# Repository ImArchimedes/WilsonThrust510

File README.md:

# WilsonThrust510
DIY PC Flight Simulator Throttle.

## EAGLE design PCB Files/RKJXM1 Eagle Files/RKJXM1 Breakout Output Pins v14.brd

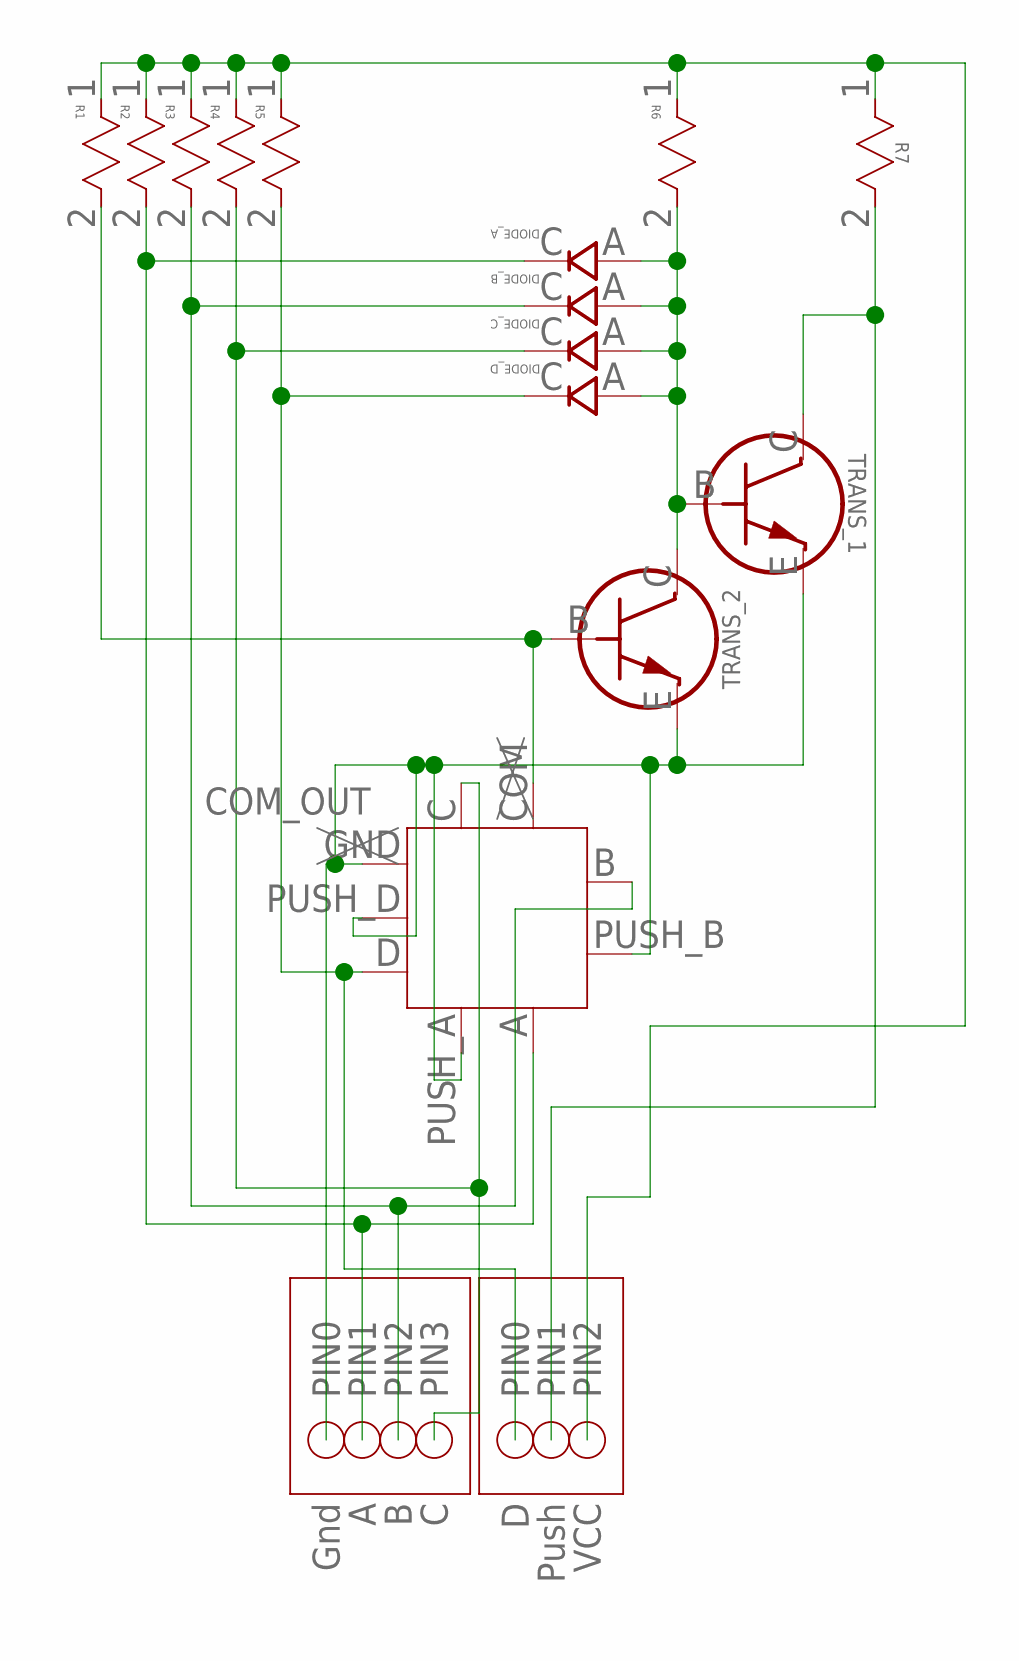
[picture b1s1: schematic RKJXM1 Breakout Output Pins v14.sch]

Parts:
DIODE_A: DIODE_SCHOTTKY_SMD_USC_TOS
DIODE_B: DIODE_SCHOTTKY_SMD_USC_TOS
DIODE_C: DIODE_SCHOTTKY_SMD_USC_TOS
DIODE_D: DIODE_SCHOTTKY_SMD_USC_TOS
R1, R2, R3, R4, R5, R6, R7: RESISTOR_1K_SMD_RNCP0805FTD1K00STA_RNCP0805_STP-L; STA_RNCP0805_STP-L
RKJXM1_SWITCH: RKJXM1_V3; RKJXM1_FOOT_V3; PART_NAME RKJXM1_Switch
TRANS_1, TRANS_2: TRANS_NPN_SMD_MMBT3904-TPSOT-23_MCC-L; SOT-23_MCC-L
U$3: JST_ZH_4PIN
U$4: JST_ZH_3PIN_NO_GND

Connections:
A_OUT: DIODE_A.C, R2.2, RKJXM1_SWITCH.A, U$3.PIN1
B_OUT: DIODE_B.C, R3.2, RKJXM1_SWITCH.B, U$3.PIN2
C_OUT: DIODE_C.C, R4.2, RKJXM1_SWITCH.C, U$3.PIN3
D_OUT: DIODE_D.C, R5.2, RKJXM1_SWITCH.D, U$4.PIN0
GROUND_OUT: RKJXM1_SWITCH.GND, RKJXM1_SWITCH.PUSH_A, RKJXM1_SWITCH.PUSH_B, RKJXM1_SWITCH.PUSH_D, TRANS_1.E, TRANS_2.E, U$3.PIN0
unnamed: R1.2, RKJXM1_SWITCH.COM, TRANS_2.B
unnamed: DIODE_A.A, DIODE_B.A, DIODE_C.A, DIODE_D.A, R6.2, TRANS_1.B, TRANS_2.C
PUSH_OUT: R7.2, TRANS_1.C, U$4.PIN1
VCC_OUT: R1.1, R2.1, R3.1, R4.1, R5.1, R6.1, R7.1, U$4.PIN2

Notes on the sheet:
COM_OUT
VCC
Push
Gnd

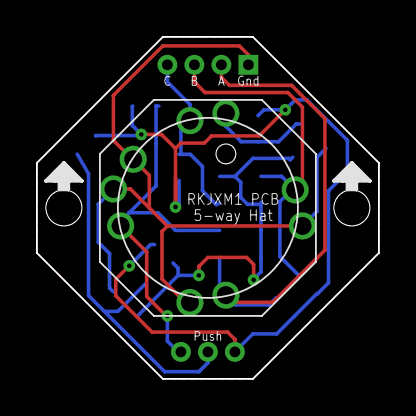
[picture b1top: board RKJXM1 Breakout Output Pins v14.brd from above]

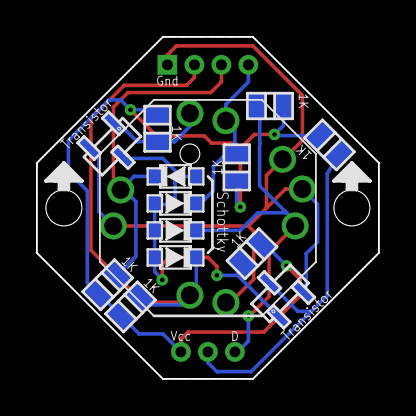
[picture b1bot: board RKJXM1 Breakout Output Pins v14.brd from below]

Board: 2 copper layers, 19.0 x 19.0 mm, 16 parts (15 on the bottom side), 9 nets.

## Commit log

2021-10-31 Added BOM
    This is the BOM with prices attached
2021-10-31 Adding PCB Files
    These are zipped up Gerber/CAM files for ordering PCBs online.
2021-10-31 Adding PCB files
    These are zips of Gerber/CAM files from Eagle and can be used to order the PCBs online.
2021-11-01 Added Print Files
    41 Files added
2022-04-18 Updated Docs
    Updated Bill of Material v3
2022-04-18 Updated BoMs
    Updated BoM and created a version with and without Grip LEDs.
2022-04-18 Updated Printable Parts
    Added latest printable parts for v.121 in both 3mf and Stl formats. Also added Fusion Project file.
2022-04-18 Renders
    Added latest renders. Small resolution as Fusion local render isn't working so I did in canvas render and took screenshot.
2022-04-19 Documentation Printed Parts
    Took all screenshots and created the first guide document, Wilson Thrust Printed Parts Guide. This walks user through printing all parts and adding inserts, UHMW tape, leather, and ferrous wire to th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
2022-06-27 Updated gates, hats, and contactless sensors
    - Hat Gates filleted from .25 to .5mm
    - Hat Stem corners filleted from .25 to .5mm
    - Thumb Button 2 threaded cover height increased by .5mm.
    - All resin push buttons on grip designed for LEDs
    - Swapped potentiometers for side and main throttles for AS5600 contactless sensors.
    - Palm button under leather now round.
2022-06-30 New Docs
    Version for of the BOM Created with a full overhaul
2022-06-30 Failed Commit Fixes
2022-06-30 failed commit fix 2
2022-06-30 commit fix 3
2022-06-30 Finalized BOM v4 LED
    Finalized BOM v4 with LEDS by:
    - Fixing links
    - Updating costs
    - Overhauling formatting
2022-07-05 Cheaper BOM and BOM Update
    Created Cheaper BOM doc and updated BOM for Grip LEDs with suggestions made by 0nn0.
2022-07-07 PCB Files updated and Docs folder reorganized.
2022-07-08 Added PCB Files
2023-03-23 Moved videos and added Hat BOMs
    Moved Tutorial videos and added BOMs for hat switches
2023-03-23 BOM Fix
    Trying to get xlsx to show
2023-05-22 Folder Structure and Doc Prep
    Added orientation pics
    Added new print parts
    Cleaned up folders
    Prepping to create Wiki
2023-05-23 Thumbnails added
    Added video thumbnails and moved print orientation images
2023-05-23 adding renders
2023-05-23 One more render added
2023-05-23 hmmmmm
2023-05-23 Added Thumbnails for Version Options
2023-05-24 BOM Updates
2023-06-06 Organizing Print Files
2023-06-06 Added Orientation Thumbs
2023-07-05 Create Main Throttle_Grip_Input Caps_Resin_5way Hat_Edged Dome.3mf
    Added Edged Dome
2023-07-28 Fixed Box Bottom Shell
2023-07-28 PCB file names updated
2023-07-28 Names updated again
2023-07-28 Replace Joystick PCB file.
    I had the old joystick pcb in the main folder and the CK_THB001P zip wasn't even in the folder.
2023-07-28 Grip PCBs Renamed
    Hopefully for the last time.
2023-07-28 Detent renaming

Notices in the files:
parts and their libraries:
COPYRIGHT: Copyright (C) 2018 Accelerated Designs. All rights reserved
